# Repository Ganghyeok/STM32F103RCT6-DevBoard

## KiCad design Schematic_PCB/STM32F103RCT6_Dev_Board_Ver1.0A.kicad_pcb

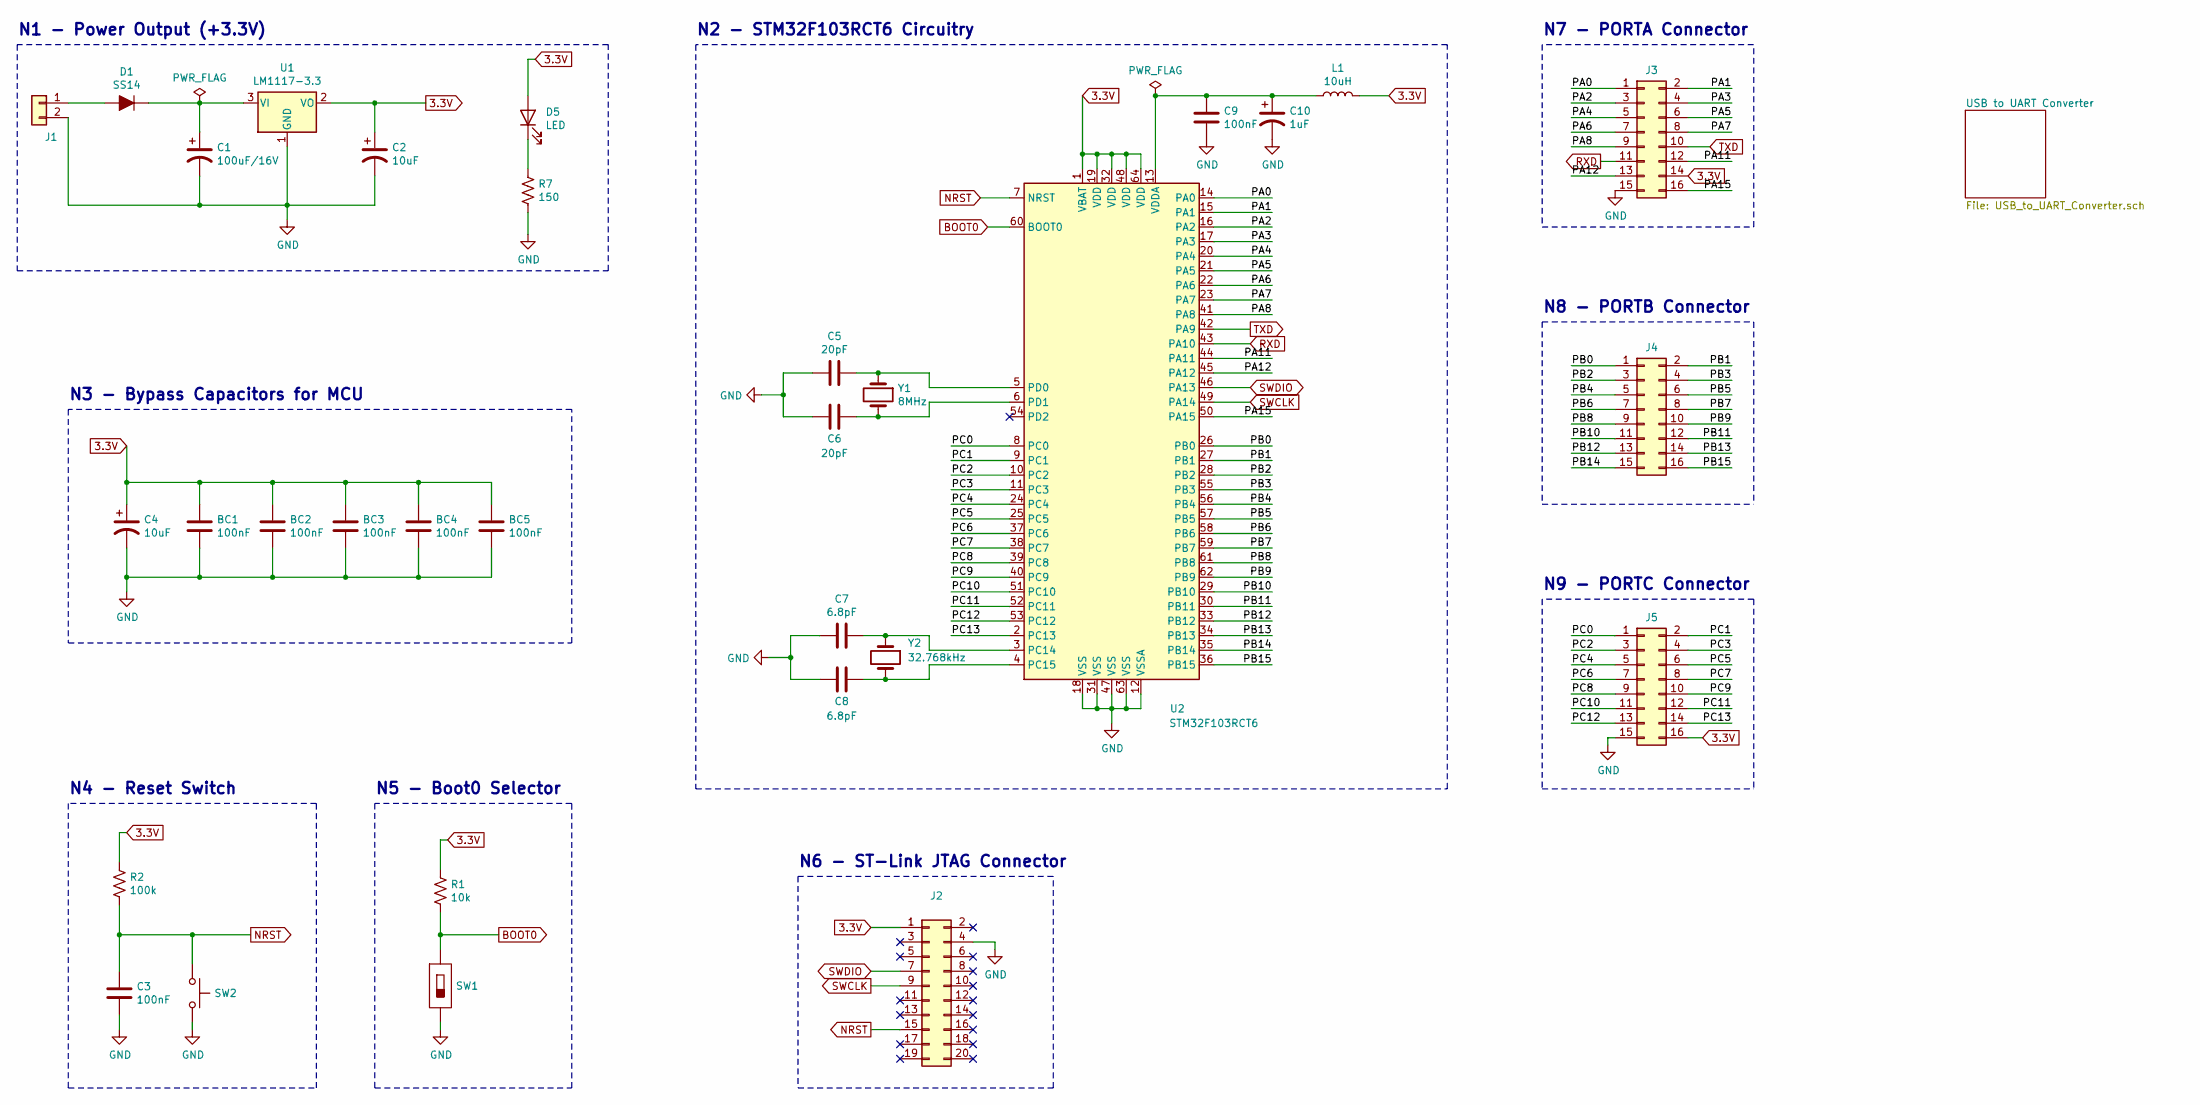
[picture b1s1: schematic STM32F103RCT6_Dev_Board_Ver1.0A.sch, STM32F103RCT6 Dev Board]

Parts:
BC1, BC2, BC3, BC4, BC5: 100nF; C_1206_3216Metric_Pad1.33x1.80mm_HandSolder
C1: 100uF/16V; C_Elec_6.3x5.4
C2, C4: 10uF; CP_EIA-3216-18_Kemet-A_Pad1.58x1.35mm_HandSolder
C3, C9: 100nF; C_1206_3216Metric_Pad1.33x1.80mm_HandSolder
C5, C6: 20pF; C_1206_3216Metric_Pad1.33x1.80mm_HandSolder
C7, C8: 6.8pF; C_1206_3216Metric_Pad1.33x1.80mm_HandSolder
C10: 1uF; CP_EIA-3216-18_Kemet-A_Pad1.58x1.35mm_HandSolder
D1: SS14; DO-214AC; MPN SS14; Digi-Key_PN SS14CT-ND
D5: LED; LED_1206_3216Metric_Pad1.42x1.75mm_HandSolder
J1: Conn_01x02; CON_2P_GH
J2: Conn_02x10_Odd_Even; HIF3F-20PA-2.54DSA_GH
J3, J4, J5: Conn_02x08_Odd_Even; PinSocket_2x08_P2.54mm_Vertical
L1: 10uH; L_1206_3216Metric_Pad1.22x1.90mm_HandSolder
R1: 10k; R_1206_3216Metric_Pad1.30x1.75mm_HandSolder
R2: 100k; R_1206_3216Metric_Pad1.30x1.75mm_HandSolder
R7: 150; R_1206_3216Metric_Pad1.30x1.75mm_HandSolder
SW1: SW_Slide_2P_SMD_GH; SW_Slide_6P_SMD_GH
SW2: SW_Push; SW_TACT_SMD_W3.9mm_L2.9mm_H2mm_GH
U1: LM1117-3.3; SOT-223
U2: STM32F103RCT6; LQFP-64_10x10mm_P0.5mm
Y1: 8MHz; CRYSTAL_HC49_SMD
Y2: 32.768kHz; Crystal_DS15_D1.5mm_L5.0mm_Horizontal

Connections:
3.3V: BC1.1, BC2.1, BC3.1, BC4.1, BC5.1, C2.1, C4.1, D5.2 (A), J2.1, J3.14, J5.16, L1.2, R1.1, R2.1, U1.2 (VO), U2.1 (VBAT), U2.19 (VDD), U2.32 (VDD), U2.48 (VDD), U2.64 (VDD); also elsewhere on the board
/PA0: J3.1, U2.14 (PA0)
/PA1: J3.2, U2.15 (PA1)
/PA2: J3.3, U2.16 (PA2)
/PA3: J3.4, U2.17 (PA3)
/PA4: J3.5, U2.20 (PA4)
/PA5: J3.6, U2.21 (PA5)
/PA6: J3.7, U2.22 (PA6)
/PA7: J3.8, U2.23 (PA7)
/PA8: J3.9, U2.41 (PA8)
/PA11: J3.12, U2.44 (PA11)
/PA12: J3.13, U2.45 (PA12)
/PA15: J3.16, U2.50 (PA15)
/PB0: J4.1, U2.26 (PB0)
/PB1: J4.2, U2.27 (PB1)
/PB2: J4.3, U2.28 (PB2)
/PB3: J4.4, U2.55 (PB3)
/PB4: J4.5, U2.56 (PB4)
/PB5: J4.6, U2.57 (PB5)
/PB6: J4.7, U2.58 (PB6)
/PB7: J4.8, U2.59 (PB7)
/PB8: J4.9, U2.61 (PB8)
/PB9: J4.10, U2.62 (PB9)
/PB10: J4.11, U2.29 (PB10)
/PB11: J4.12, U2.30 (PB11)
/PB12: J4.13, U2.33 (PB12)
/PB13: J4.14, U2.34 (PB13)
/PB14: J4.15, U2.35 (PB14)
/PB15: J4.16, U2.36 (PB15)
/PC0: J5.1, U2.8 (PC0)
/PC1: J5.2, U2.9 (PC1)
/PC2: J5.3, U2.10 (PC2)
/PC3: J5.4, U2.11 (PC3)
/PC4: J5.5, U2.24 (PC4)
/PC5: J5.6, U2.25 (PC5)
/PC6: J5.7, U2.37 (PC6)
/PC7: J5.8, U2.38 (PC7)
/PC8: J5.9, U2.39 (PC8)
/PC9: J5.10, U2.40 (PC9)
/PC10: J5.11, U2.51 (PC10)
/PC11: J5.12, U2.52 (PC11)
/PC12: J5.13, U2.53 (PC12)
/PC13: J5.14, U2.2 (PC13)
BOOT0: R1.2, SW1.1, U2.60 (BOOT0)
GND: BC1.2, BC2.2, BC3.2, BC4.2, BC5.2, C1.2, C2.2, C3.2, C4.2, C5.2, C6.2, C7.2, C8.2, C9.2, C10.2, J1.2, J2.4, J3.15, J5.15, R7.2, SW1.2, SW2.2, U1.1 (GND), U2.12 (VSSA), U2.18 (VSS), U2.31 (VSS), U2.47 (VSS), U2.63 (VSS); also elsewhere on the board
NRST: C3.1, J2.15, R2.2, SW2.1, U2.7 (NRST)
unnamed: C1.1, D1.K, U1.3 (VI)
unnamed: C5.1, U2.5 (PD0), Y1.1
unnamed: C6.1, U2.6 (PD1), Y1.2
unnamed: C7.1, U2.3 (PC14), Y2.1
unnamed: C8.1, U2.4 (PC15), Y2.2
unnamed: C9.1, C10.1, L1.1, U2.13 (VDDA)
unnamed: D1.A, J1.1
unnamed: D5.1 (K), R7.1
RXD: J3.11, U2.43 (PA10); also elsewhere on the board
SWCLK: J2.9, U2.49 (PA14)
SWDIO: J2.7, U2.46 (PA13)
TXD: J3.10, U2.42 (PA9); also elsewhere on the board

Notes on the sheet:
N1 - Power Output (+3.3V)
N2 - STM32F103RCT6 Circuitry
N4 - Reset Switch
N5 - Boot0 Selector
N3 - Bypass Capacitors for MCU
N6 - ST-Link JTAG Connector
N7 - PORTA Connector
N8 - PORTB Connector
N9 - PORTC Connector

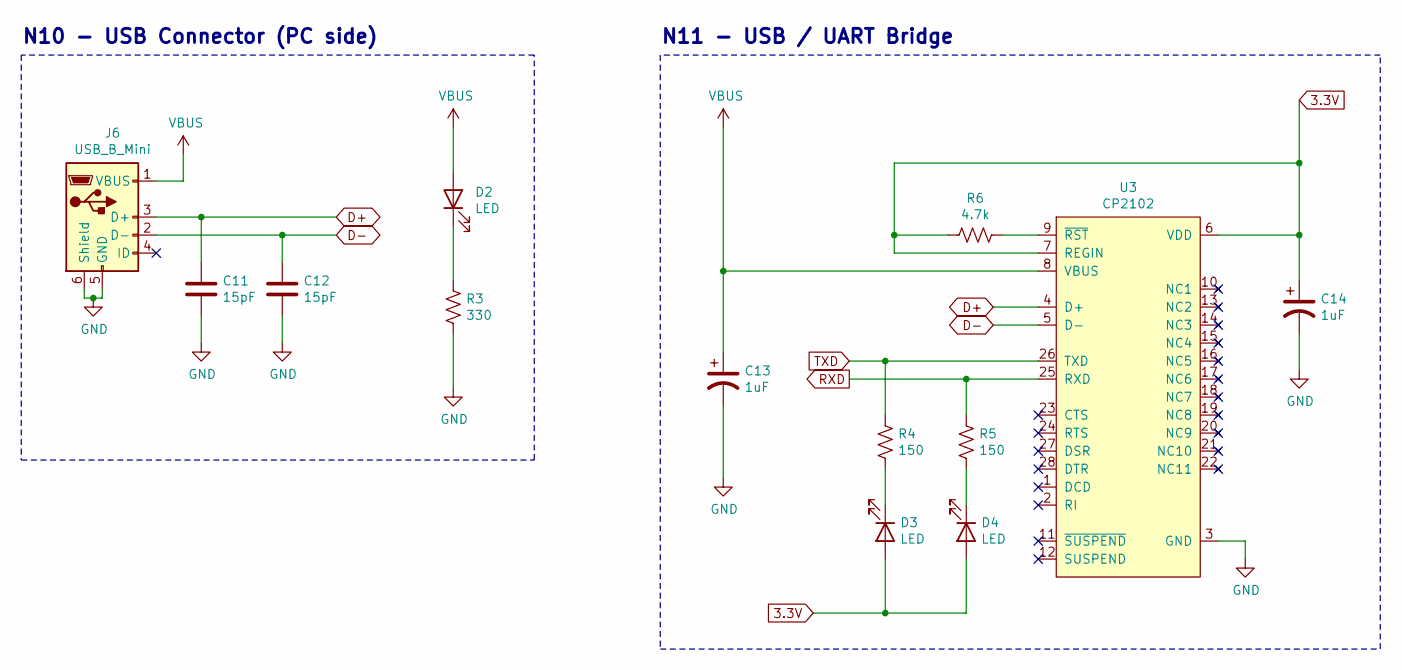
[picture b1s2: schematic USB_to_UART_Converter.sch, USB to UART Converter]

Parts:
C11, C12: 15pF; C_1206_3216Metric_Pad1.33x1.80mm_HandSolder
C13, C14: 1uF; CP_EIA-3216-18_Kemet-A_Pad1.58x1.35mm_HandSolder
D2, D3, D4: LED; LED_1206_3216Metric_Pad1.42x1.75mm_HandSolder
J6: USB_B_Mini; USB_Mini-B_Lumberg_2486_01_Horizontal
R3: 330; R_1206_3216Metric_Pad1.30x1.75mm_HandSolder
R4, R5: 150; R_1206_3216Metric_Pad1.30x1.75mm_HandSolder
R6: 4.7k; R_1206_3216Metric_Pad1.30x1.75mm_HandSolder
U3: CP2102; VFQFN-28-1EP_5x5mm_HandSolder

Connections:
3.3V: C14.1, D3.2 (A), D4.2 (A), R6.1, U3.6 (VDD), U3.7 (REGIN); also elsewhere on the board
D+: C11.1, J6.3 (D+), U3.4 (D+)
D-: C12.1, J6.2 (D-), U3.5 (D-)
GND: C11.2, C12.2, C13.2, C14.2, J6.5 (GND), J6.6 (Shield), R3.1, U3.3 (GND); also elsewhere on the board
unnamed: D2.1 (K), R3.2
unnamed: D3.1 (K), R4.1
unnamed: D4.1 (K), R5.1
unnamed: R6.2, U3.9 (~RST)
RXD: R5.2, U3.25 (RXD); also elsewhere on the board
TXD: R4.2, U3.26 (TXD); also elsewhere on the board
VBUS: C13.1, D2.2 (A), J6.1 (VBUS), U3.8 (VBUS)

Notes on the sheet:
N10 - USB Connector (PC side)
N11 - USB / UART Bridge

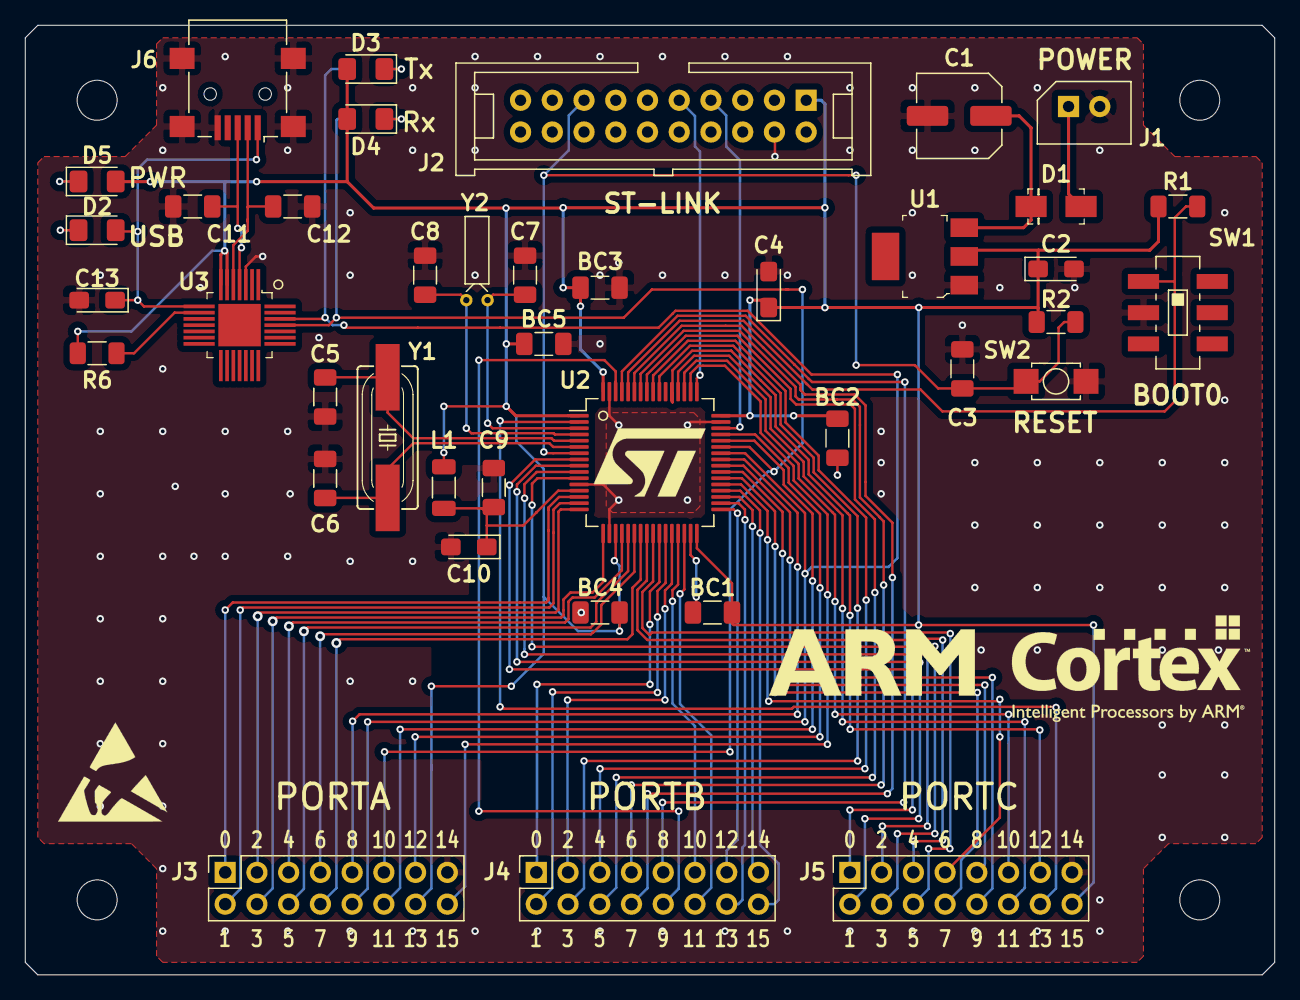
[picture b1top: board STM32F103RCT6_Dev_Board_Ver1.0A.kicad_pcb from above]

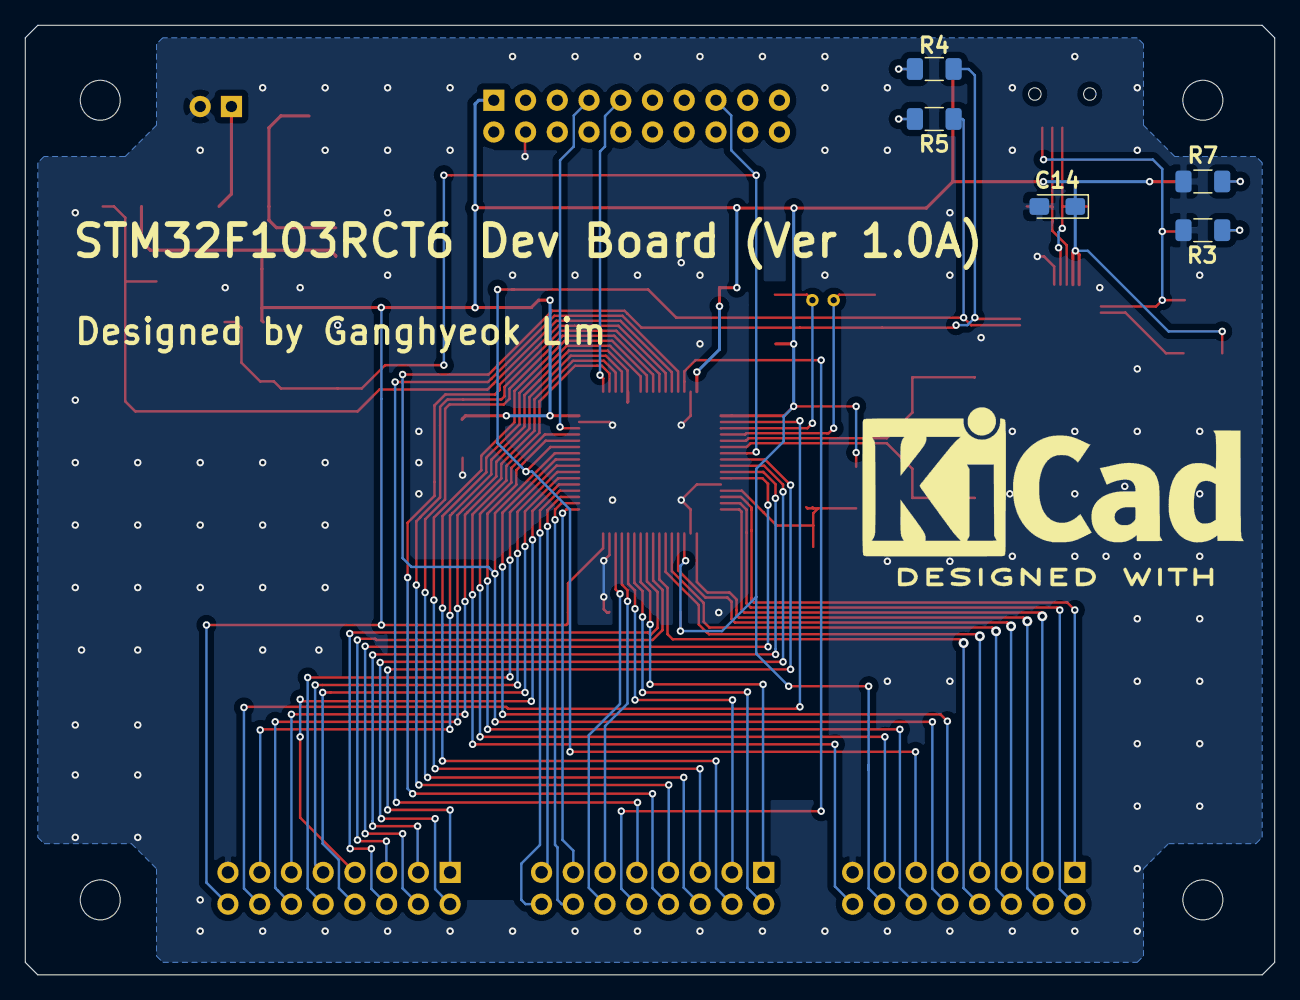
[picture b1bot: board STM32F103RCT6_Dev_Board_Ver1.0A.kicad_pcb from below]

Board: 2 copper layers, 100.0 x 76.0 mm, 45 parts (5 on the bottom side), 65 nets.

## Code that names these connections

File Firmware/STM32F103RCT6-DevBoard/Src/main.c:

/**
 ******************************************************************************
 * @file           : main.c
 * @author         : Auto-generated by STM32CubeIDE
 * @brief          : Main program body
 ******************************************************************************
 * @attention
 *
 * <h2><center>&copy; Copyright (c) 2019 STMicroelectronics.
 * All rights reserved.</center></h2>
 *
 * This software component is licensed by ST under BSD 3-Clause license,
 * the "License"; You may not use this file except in compliance with the
 * License. You may obtain a copy of the License at:
 *                        opensource.org/licenses/BSD-3-Clause
 *
 ******************************************************************************
 */

/*
 *  TIM1_CH1 : PA8
 *  TIM1_CH2 : PA9
 *  TIM1_CH3 : PA10
 *  TIM1_CH4 : PA11
 *  -> Output Compare channel -> AF Push-Pull
 */


#include "stm32f103xx.h"


void GPIO_LEDInit(GPIO_HandleTypeDef *pGPIOHandle);
void USART1_Init(UART_HandleTypeDef *pUSARTHandle);
void TIM1_Init(TIM_HandleTypeDef *pTIMHandle);

UART_HandleTypeDef USART1Handle;
TIM_HandleTypeDef TIMHandle;

//char str1[15] = "Hello World!\n\r";
//char str2[17] = "VAPALUX_Clever\n\r";


int main(void)
{
	//memset(&USART1Handle, 0, sizeof(USART1Handle));

	SystemClock_Config(SYSCLK_FREQ_72MHZ);		// Other SYSCLK options are available

	// 1. Low level initialization of UART with GPIO clock enable
	//USART_LowInit(USART1);

	// 2. UART initialization with UART Clock enable
	//USART1_Init(&USART1Handle);

	//NVIC_IRQConfig(IRQ_NO_USART1, NVIC_PRIOR_8, ENABLE);

	Delay_ms(10);

	/* ---------------------------------------------------------------------------- */

	memset(&TIMHandle, 0, sizeof(TIMHandle));

	TIM1_Init(&TIMHandle);

	TIM_PWM_Start(&TIMHandle, TIM_CHANNEL_1);
	TIM_PWM_Start(&TIMHandle, TIM_CHANNEL_2);
	TIM_PWM_Start(&TIMHandle, TIM_CHANNEL_3);
	TIM_PWM_Start(&TIMHandle, TIM_CHANNEL_4);

	while(1);
}


void GPIO_LEDInit(GPIO_HandleTypeDef *pGPIOHandle)
{
	pGPIOHandle->Instance = GPIOA;
	pGPIOHandle->Init.Mode = GPIO_MODE_OUTPUT_PP;
	pGPIOHandle->Init.Pin = GPIO_PIN_0;
	pGPIOHandle->Init.Pull = GPIO_NOPULL;
	pGPIOHandle->Init.Speed = GPIO_SPEED_FREQ_LOW;

	GPIO_Init(GPIOA, &pGPIOHandle->Init);
}


void USART1_Init(UART_HandleTypeDef *pUSARTHandle)
{
	pUSARTHandle->Instance = USART1;
	pUSARTHandle->Init.Mode = UART_MODE_TX;
	pUSARTHandle->Init.BaudRate = USART_STD_BAUD_115200;
	pUSARTHandle->Init.OverSampling = UART_OVERSAMPLING_16;
	pUSARTHandle->Init.HwFlowCtl = UART_HWCONTROL_NONE;
	pUSARTHandle->Init.Parity = UART_PARITY_NONE;
	pUSARTHandle->Init.StopBits = UART_STOPBITS_1;
	pUSARTHandle->Init.WordLength = UART_WORDLENGTH_8B;
	pUSARTHandle->State = USART_STATE_READY;

	USART_Init(pUSARTHandle);
}


void TIM1_Init(TIM_HandleTypeDef *pTIMHandle)
{
	// TIM Init Structure config
	pTIMHandle->Instance = TIM1;
	pTIMHandle->Init.Prescaler = (720-1);  //   72MHz / 720 = 100kHz
	pTIMHandle->Init.Period = (10-1);  //   100kHz / 10 = 10kHz
	// TIM Base Initialization
	TIM_BaseInit(pTIMHandle);

	// TIM Low level Initialization
	TIM_LowInit(pTIMHandle->Instance);

	TIM_OC_InitTypeDef TIM1_PWMConfig;
	memset(&TIM1_PWMConfig, 0, sizeof(TIM1_PWMConfig));

	// TIM_PWM_Config
	TIM1_PWMConfig.OCMode = TIM_OCMODE_PWM1;
	TIM1_PWMConfig.OCPolarity = TIM_OCPOLARITY_HIGH;
	TIM1_PWMConfig.Pulse = 2;	// 20% duty
	TIM_PWM_ConfigChannel(pTIMHandle, &TIM1_PWMConfig, TIM_CHANNEL_1);

	TIM1_PWMConfig.OCMode = TIM_OCMODE_PWM1;
	TIM1_PWMConfig.OCPolarity = TIM_OCPOLARITY_HIGH;
	TIM1_PWMConfig.Pulse = 4;	// 40% duty
	TIM_PWM_ConfigChannel(pTIMHandle, &TIM1_PWMConfig, TIM_CHANNEL_2);

	TIM1_PWMConfig.OCMode = TIM_OCMODE_PWM1;
	TIM1_PWMConfig.OCPolarity = TIM_OCPOLARITY_HIGH;
	TIM1_PWMConfig.Pulse = 6;	// 60% duty
	TIM_PWM_ConfigChannel(pTIMHandle, &TIM1_PWMConfig, TIM_CHANNEL_3);

	TIM1_PWMConfig.OCMode = TIM_OCMODE_PWM1;
	TIM1_PWMConfig.OCPolarity = TIM_OCPOLARITY_HIGH;
	TIM1_PWMConfig.Pulse = 8;	// 80% duty
	TIM_PWM_ConfigChannel(pTIMHandle, &TIM1_PWMConfig, TIM_CHANNEL_4);
}

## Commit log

2020-12-01 Add PCB files that have already been produced and tested
2020-12-01 Add HW/FW documents
2020-12-01 Create STM32 project(FW)
2020-12-02 Create MCU specific Header file(stm32f103xx.h)
2020-12-03 TEST System Clock configuration of PLL out
    - Add Test code of System Clock of MCU to check whether it is PLL output or not
    - Update stm32f103xx.h
    : Replace Kiran style contents with HAL style contents
    - Update stm32f103xx_rcc_driver.c, .h
    : Replace Kiran style contents with HAL style contents
2020-12-05 [Add & Test] GPIO driver
    - Add GPIO_Init
    GPIO_ReadPin
    GPIO_WritePin
    GPIO_TogglePin
    NVIC_IRQConfig
    - Test (PASS) GPIO port initialization
2020-12-06 [Update] delay function with high accuracy
    - Add Memory mapping of Core Hardware, including SysTick timer's (stm32f103xx.h)
    Peripheral Declarations of Core Hardware, including SysTick timer's (core.h)
    SysTick structure type (core.h)
    - Relocation NVIC structure type / NVIC_IRQConfig function (to core.h, core.c)
    - Update delay functions (Delay_us, Delay_ms)
    - Test Toggle LED with updated delay functions
2020-12-11 [Add & Test] UART Transmit by Polling mode
    - Add USART driver file (stm32f103xx_usart_driver.h, .c)
    RCC_GetPLLOutputClock function
    RCC_GetPCLKxValue function
    - Test (PASS) UART Transmit data to PC (Polling mode)
2020-12-11 [Add & Test] UART Transmit by Interrupt mode
    - Add USART_Transmit_IT
    - Test (PASS) UART Transmit by Interrupt mode
2020-12-15 [Add & Test] TIM Base interrupt generation
    - Add TIM driver file (stm32f103xx_tim_driver.h, .c)
    - Test (PASS) TIM Base 1Hz interrupt generation
2020-12-17 [Add & Test] TIM PWM generation for ch1~4
    - Add TIM PWM related functions
    - Test (PASS) TIM PWM generation for ch1~4 with arbitrary duty
